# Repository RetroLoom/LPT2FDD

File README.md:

# LPT2FDD
LPT to Floppy Drive adapter for supported vintage laptops. This revision is specifically designed for the Sharp PC-9000 / 9030 series laptops but may also work on clones or subsequent Sharp laptops as well. The laptop must support floppy protocol through the LPT port for this to work. This project also serves as an archive for pin sets required for LPT floppy protocols.

v0.5 Adds a jumper resistor between pins 21 and 22 to allow compatibility with Compaq laptop external floppy detection. Currently it is recommended to use a 1k resistor for extra safety. This should trigger the Compaq laptop to recognize a connected floppy drive (if supported by laptop), but external power needs to be provided separately to the floppy drive. 

More information and discussion can be found here - https://www.vogons.org/viewtopic.php?t=105093.
 
## Build of Materials and Installation
Other than the PCB, there are really only two other connectors required to build the LPT2FDD.
Use with a standard single drive floppy cable with the twist. Powering the floppy drive externally is required. A ps/2 to 5v adapter will be provided soon.

Pin 3 of the DC3 connector may need to be removed for keyed floppy cables. 

### Example Sources
34-Pin DC3 Connector
https://www.aliexpress.us/item/3256806835271080.html?spm=a2g0o.order_list.order_list_main.110.1ec5180292mWAN&gatewayAdapt=glo2usa

D-SUB DB-25 Male or Female
https://www.aliexpress.us/item/3256805300852948.html?spm=a2g0o.order_list.order_list_main.121.1ec5180292mWAN&gatewayAdapt=glo2usa

Single Drive Floppy cable
https://www.aliexpress.us/item/3256805300852948.html?spm=a2g0o.order_list.order_list_main.121.1ec5180292mWAN&gatewayAdapt=glo2usa

## Support the Developer
This project is brought to you free and open source, but it is not free to develop. If you like this project please consider supporting this and future developments. 

https://www.patreon.com/RetroLoom

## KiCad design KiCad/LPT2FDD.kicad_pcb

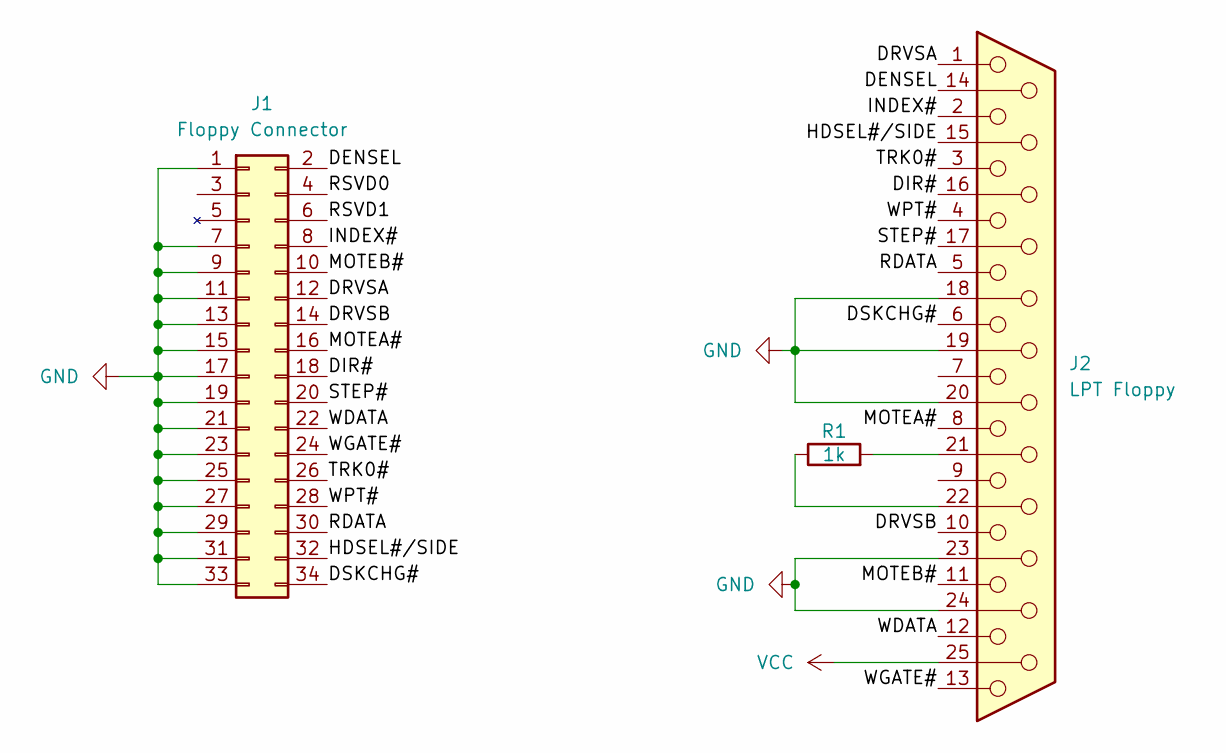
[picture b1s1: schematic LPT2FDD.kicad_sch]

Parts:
J1: Floppy Connector; IDC-Header_2x17_P2.54mm_Vertical
J2: LPT Floppy; DSUB-25_Male_Horizontal_P2.77x2.84mm_EdgePinOffset4.94mm_Ho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
R1: 1k; R_0805_2012Metric_Pad1.20x1.40mm_HandSolder

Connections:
/DENSEL: J1.2 (DENSEL), J2.14 (DENSEL)
/DIR#: J1.18 (DIR#), J2.16 (-DIR)
/DRVSA: J1.12 (DRVSB), J2.1 (-DSO)
/DRVSB: J1.14 (DRVSA), J2.10 (-DS1)
/DSKCHG#: J1.34 (DSKCHG#), J2.6 (-DSKCHG)
/HDSEL#/SIDE: J1.32 (HDSEL#/SIDE), J2.15 (-HDSEL)
/INDEX#: J1.8 (INDEX#), J2.2 (-INDEX)
/MOTEA#: J1.16 (MOTEB#), J2.8 (-MTR0)
/MOTEB#: J1.10 (MOTEA#), J2.11 (-MTR1)
/RDATA: J1.30 (RDATA), J2.5 (-RDATA)
/RSVD0: J1.4 (RSVD)
/RSVD1: J1.6 (RSVD)
/STEP#: J1.20 (STEP#), J2.17 (-STEP)
/TRK0#: J1.26 (TRK0#), J2.3 (-TRK0)
/WDATA: J1.22 (WDATA), J2.12 (-WDATA)
/WGATE#: J1.24 (WGATE#), J2.13 (-WGATE)
/WPT#: J1.28 (WPT#), J2.4 (-WP)
GND: J1.1 (GND), J1.7 (GND), J1.9 (GND), J1.11 (GND), J1.13 (GND), J1.15 (GND), J1.17 (GND), J1.19 (GND), J1.21 (GND), J1.23 (GND), J1.25 (GND), J1.27 (GND), J1.29 (GND), J1.31 (GND), J1.33 (GND), J2.18 (GND), J2.19, J2.20, J2.23, J2.24
unnamed: J2.21, R1.2
unnamed: J2.22, R1.1
VCC: J2.25

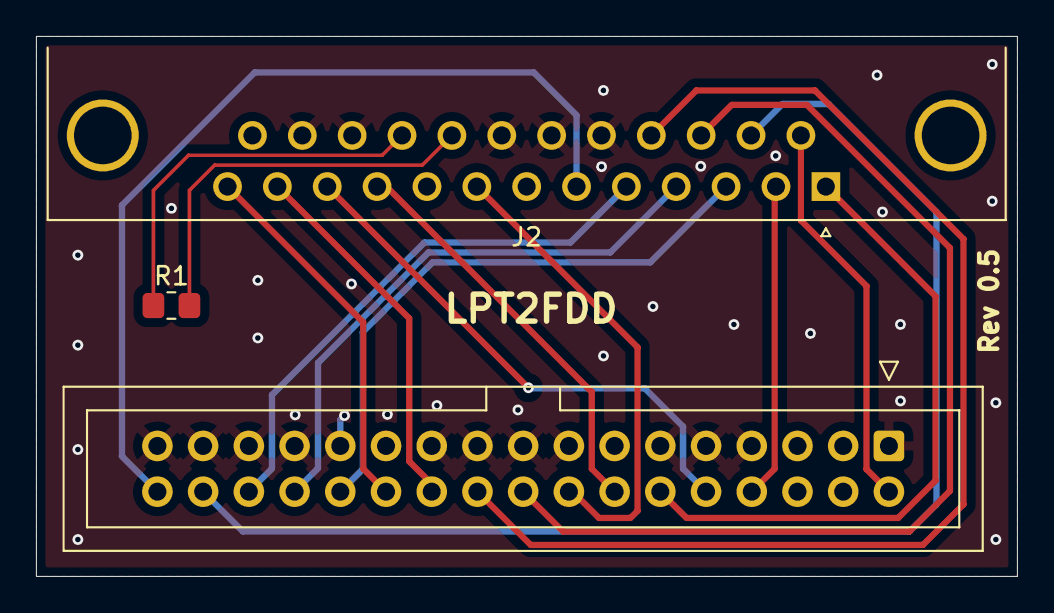
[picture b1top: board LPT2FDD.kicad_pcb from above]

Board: 2 copper layers, 54.5 x 30.0 mm, 3 parts (0 on the bottom side), 18 nets.

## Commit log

2025-01-22 Initial Design - 0.4
2025-02-16 Update readme and images
2025-02-16 Create LICENSE
2025-03-08 PS/2 Power Adapter v0.2
2026-01-21 v0.5 Add pin 21 and pin 22 jumper for Compaq compatibility
2026-01-21 PS/2 Power Adapter v0.3 - Better labeling, filename fix
